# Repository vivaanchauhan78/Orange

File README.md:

# Orange
A small MacPad for copying and pasting this macro pad cuts the key input in half by 4 keys to 2 KEYS i just remove the need for Ctrl + C and Ctrl + v!
I hated that I had to spend 3 sec of my life copying and pasteing stuff useing Ctrl + C and Ctrl + v so i came up with this now it only takes me about 6 sec!

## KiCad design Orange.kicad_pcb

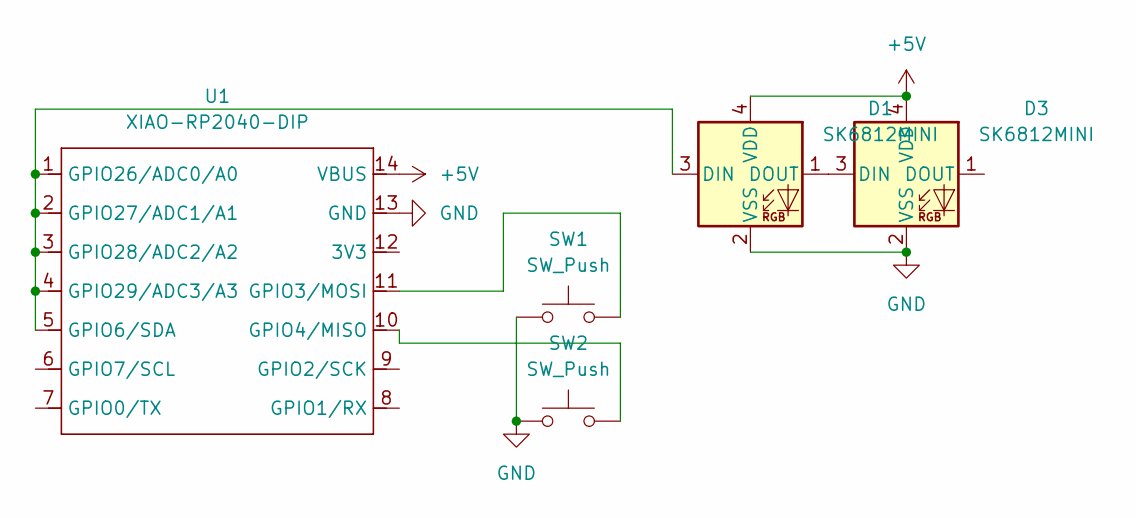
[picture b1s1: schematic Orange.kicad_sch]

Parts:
D1, D3: SK6812MINI; LED_SK6812MINI_PLCC4_3.5x3.5mm_P1.75mm
SW1, SW2: SW_Push; SW_Cherry_MX_1.00u_PCB
U1: XIAO-RP2040-DIP; XIAO-ESP32C3-DIP

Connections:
+5V: D1.4 (VDD), D3.4 (VDD), U1.14 (VBUS)
GND: D1.2 (VSS), D3.2 (VSS), SW1.1, SW2.1, U1.13 (GND)
unnamed: D1.3 (DIN), U1.1 (GPIO26/ADC0/A0), U1.2 (GPIO27/ADC1/A1), U1.3 (GPIO28/ADC2/A2), U1.4 (GPIO29/ADC3/A3), U1.5 (GPIO6/SDA)
unnamed: D1.1 (DOUT), D3.3 (DIN)
unnamed: SW1.2, U1.11 (GPIO3/MOSI)
unnamed: SW2.2, U1.10 (GPIO4/MISO)

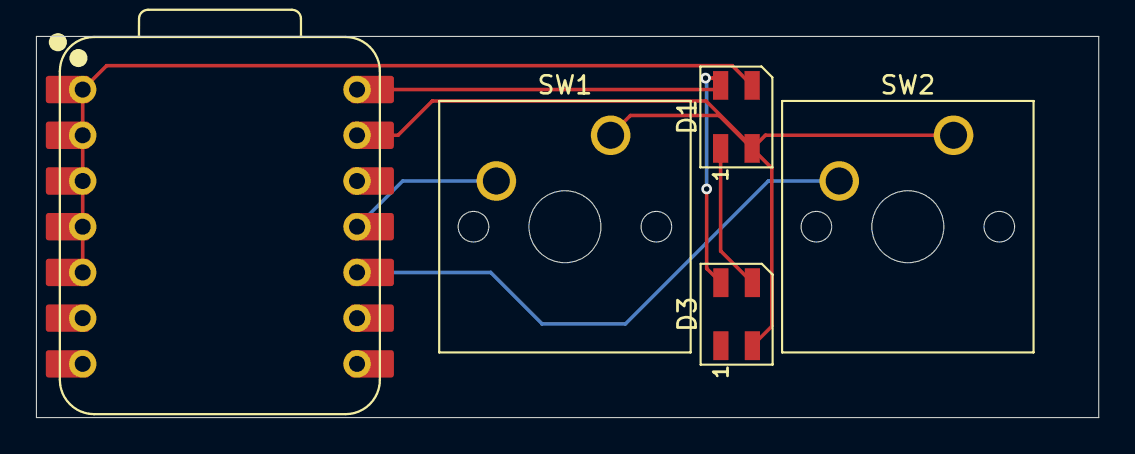
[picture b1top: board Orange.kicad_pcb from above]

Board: 2 copper layers, 59.0 x 21.2 mm, 5 parts (0 on the bottom side), 6 nets.
